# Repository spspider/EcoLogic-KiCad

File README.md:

# EcoLogic KiCad - ESP8266 Home Automation PCB

A professional-grade KiCad project for ESP8266-based home automation systems, designed for PCBWAY manufacturing and Home Assistant integration.

you can control your device throw this site:
[https://ecologic.pp.ua/iot-manager/](https://ecologic.pp.ua/iot-manager/)
Register as a new user and go to "Devices"

## 📋 Project Overview

This repository contains complete PCB designs for IoT home automation controllers using ESP8266 microcontrollers. The boards are optimized for controlling lights, home appliances, and other smart devices through Home Assistant.

### Key Features
- ESP8266-based design for WiFi connectivity
- Multiple relay outputs for appliance control
- PCBWAY-ready manufacturing files
- Home Assistant compatible
- Professional PCB layout with proper isolation
- SMD components for compact design

## 🖼️ Board Images

| Schematic | PCB Layout |
|-----------|------------|
|  |  |
|  |  |

## 📁 Repository Structure

```
EcoLogic-KiCad/
├── IoTmanager/                    # Main project directory
│   ├── BOM-CPL/                   # Bill of Materials & Component Placement
│   │   ├── BOM.csv               # PCBWAY Bill of Materials
│   │   ├── CPL.xlsx              # Component Placement List
│   │   └── *.csv                 # Position files
│   ├── gerber/                    # Manufacturing files
│   │   ├── gerber.zip            # Complete gerber package
│   │   ├── *.gbr                 # Individual gerber layers
│   │   └── *.drl                 # Drill files
│   ├── images/                    # PCB and schematic images
│   ├── LCPCB/                     # PCBWAY templates
│   └── *.kicad_*                 # KiCad project files
└── README.md                      # This file
```

## 🔧 Bill of Materials (BOM)

| Reference | Component | Quantity | Description |
|-----------|-----------|----------|-------------|
| U2 | ESP-12F | 1 | ESP8266 WiFi Module |
| U6 | AMS1117-3.3 | 1 | 3.3V Voltage Regulator |
| U12 | AMS1117-5.0 | 1 | 5.0V Voltage Regulator |
| U3 | DHT11 | 1 | Temperature & Humidity Sensor |
| U7 | DS18B20 | 1 | Temperature Sensor |
| U5 | PJ-320A | 1 | Audio Jack Connector |
| Q1,Q3,Q5,Q7 | MMBT5401 | 4 | PNP Transistors |
| Q2,Q4,Q6,Q8 | MMBT5551-npn | 4 | NPN Transistors |
| K3,K5,K6,K7 | ZC32F-012-HS3 | 4 | 12V Relays |
| D1 | LD271 | 1 | LED Indicator |
| D2,D3,D4,D5 | 1N4148 | 4 | Switching Diodes |
| C1,C2 | 1000µF | 2 | Polarized Capacitors |
| C4 | 10µF | 1 | Polarized Capacitor |
| C3 | 100nF | 1 | Ceramic Capacitor |
| R1,R5,R8,R11,R16 | 100Ω | 5 | Current Limiting Resistors |
| R3,R4,R12,R14-R19 | 1kΩ | 10 | Base Resistors |
| R2,R6,R9,R10,R13 | 10kΩ | 8 | Pull-up Resistors |
| R7 | 4.7kΩ | 1 | Pull-up Resistor |
| 33R1 | 33Ω | 1 | Current Limiting Resistor |
| J1 | Power Relay | 1 | Main Power Connector |
| J2,J3 | 12-Pin Connector | 2 | I/O Connectors |
| J4 | Flash Connector | 1 | Programming Interface |
| J5 | Reset Button | 1 | System Reset |
| SW1 | Push Button | 1 | 6mm Tactile Switch |
| Jumper-d5,d6,d7 | Jumpers | 3 | Configuration Jumpers |

## 🏭 PCBway Manufacturing Guide

### Step 1: Prepare Files
1. Download the complete `gerber.zip` from `IoTmanager/gerber/`
2. Get BOM file: `IoTmanager/BOM-CPL/BOM.csv`
3. Get CPL file: `IoTmanager/BOM-CPL/CPL.xlsx`

### Step 2: Upload to PCBWAY
1. Go to [www.pcbway.com](https://www.pcbway.com/QuickOrderOnline.aspx)

2. Click "Add gerber file" and upload `gerber2.zip`
3. Review PCB specifications, dont change anything:

   - **Layers**: 2
   - **Thickness**: 1.6mm
   - **Color**: Green (recommended)
   - **Surface Finish**: HASL (lead-free)

### Step 3: SMT Assembly (Optional)
1. Enable "SMT Assembly"
2. Upload BOM file (`BOM.csv`)
3. Upload CPL file (`CPL.xlsx`)
4. Review component placement
5. Confirm parts availability

### Step 4: Order
- Minimum quantity: 5 pieces
- Typical lead time: 2-5 days (PCB only)
- SMT assembly adds 3-5 days

## ⚡ Power Requirements

| Parameter | Value | Notes |
|-----------|-------|-------|
| Input Voltage | 5V DC | Via USB or external supply |
| Current Consumption | 80-200mA | Depends on relay states |
| Relay Switching | 10A @ 250V AC | Per relay channel |
| Logic Level | 3.3V | ESP8266 native |

## 🛠️ Assembly Tips

### Soldering Guidelines
- Use lead-free solder (SAC305 recommended)
- Soldering iron: 350°C for SMD components
- Use flux for better joints
- Solder ESP8266 module first

### Testing Procedure
1. **Visual Inspection**: Check for shorts and proper alignment
2. **Power Test**: Apply 5V and measure 3.3V rail
3. **Programming Test**: Upload basic blink sketch
4. **Relay Test**: Verify relay switching with multimeter

## 🚨 Safety Warnings

⚠️ **HIGH VOLTAGE WARNING**
- Relays switch mains voltage (110V/220V AC)
- Always disconnect power before wiring
- Use proper electrical enclosure
- Follow local electrical codes

⚠️ **ESD Precautions**
- Use anti-static wrist strap during assembly
- Store boards in anti-static bags
- Ground yourself before handling

## 📝 Version History

| Version | Date | Changes |
|---------|------|---------|
| v2 | 2025-07 | Improved routing, added protection circuits |
| v1 | 2025-05 | Initial release |

## 🤝 Contributing

1. Fork the repository
2. Create feature branch (`git checkout -b feature/improvement`)
3. Commit changes (`git commit -am 'Add improvement'`)
4. Push to branch (`git push origin feature/improvement`)
5. Create Pull Request

## 📄 License

This project is open-source hardware. Feel free to modify and distribute according to your needs.

## 🆘 Support & Donations

If this project helped you, consider supporting the development:

**Other ways to support:**
- ⭐ Star this repository
- 🐛 Report bugs and issues
- 💡 Suggest improvements
- 📖 Improve documentation
---

**Made with ❤️ for the Home Automation Community**

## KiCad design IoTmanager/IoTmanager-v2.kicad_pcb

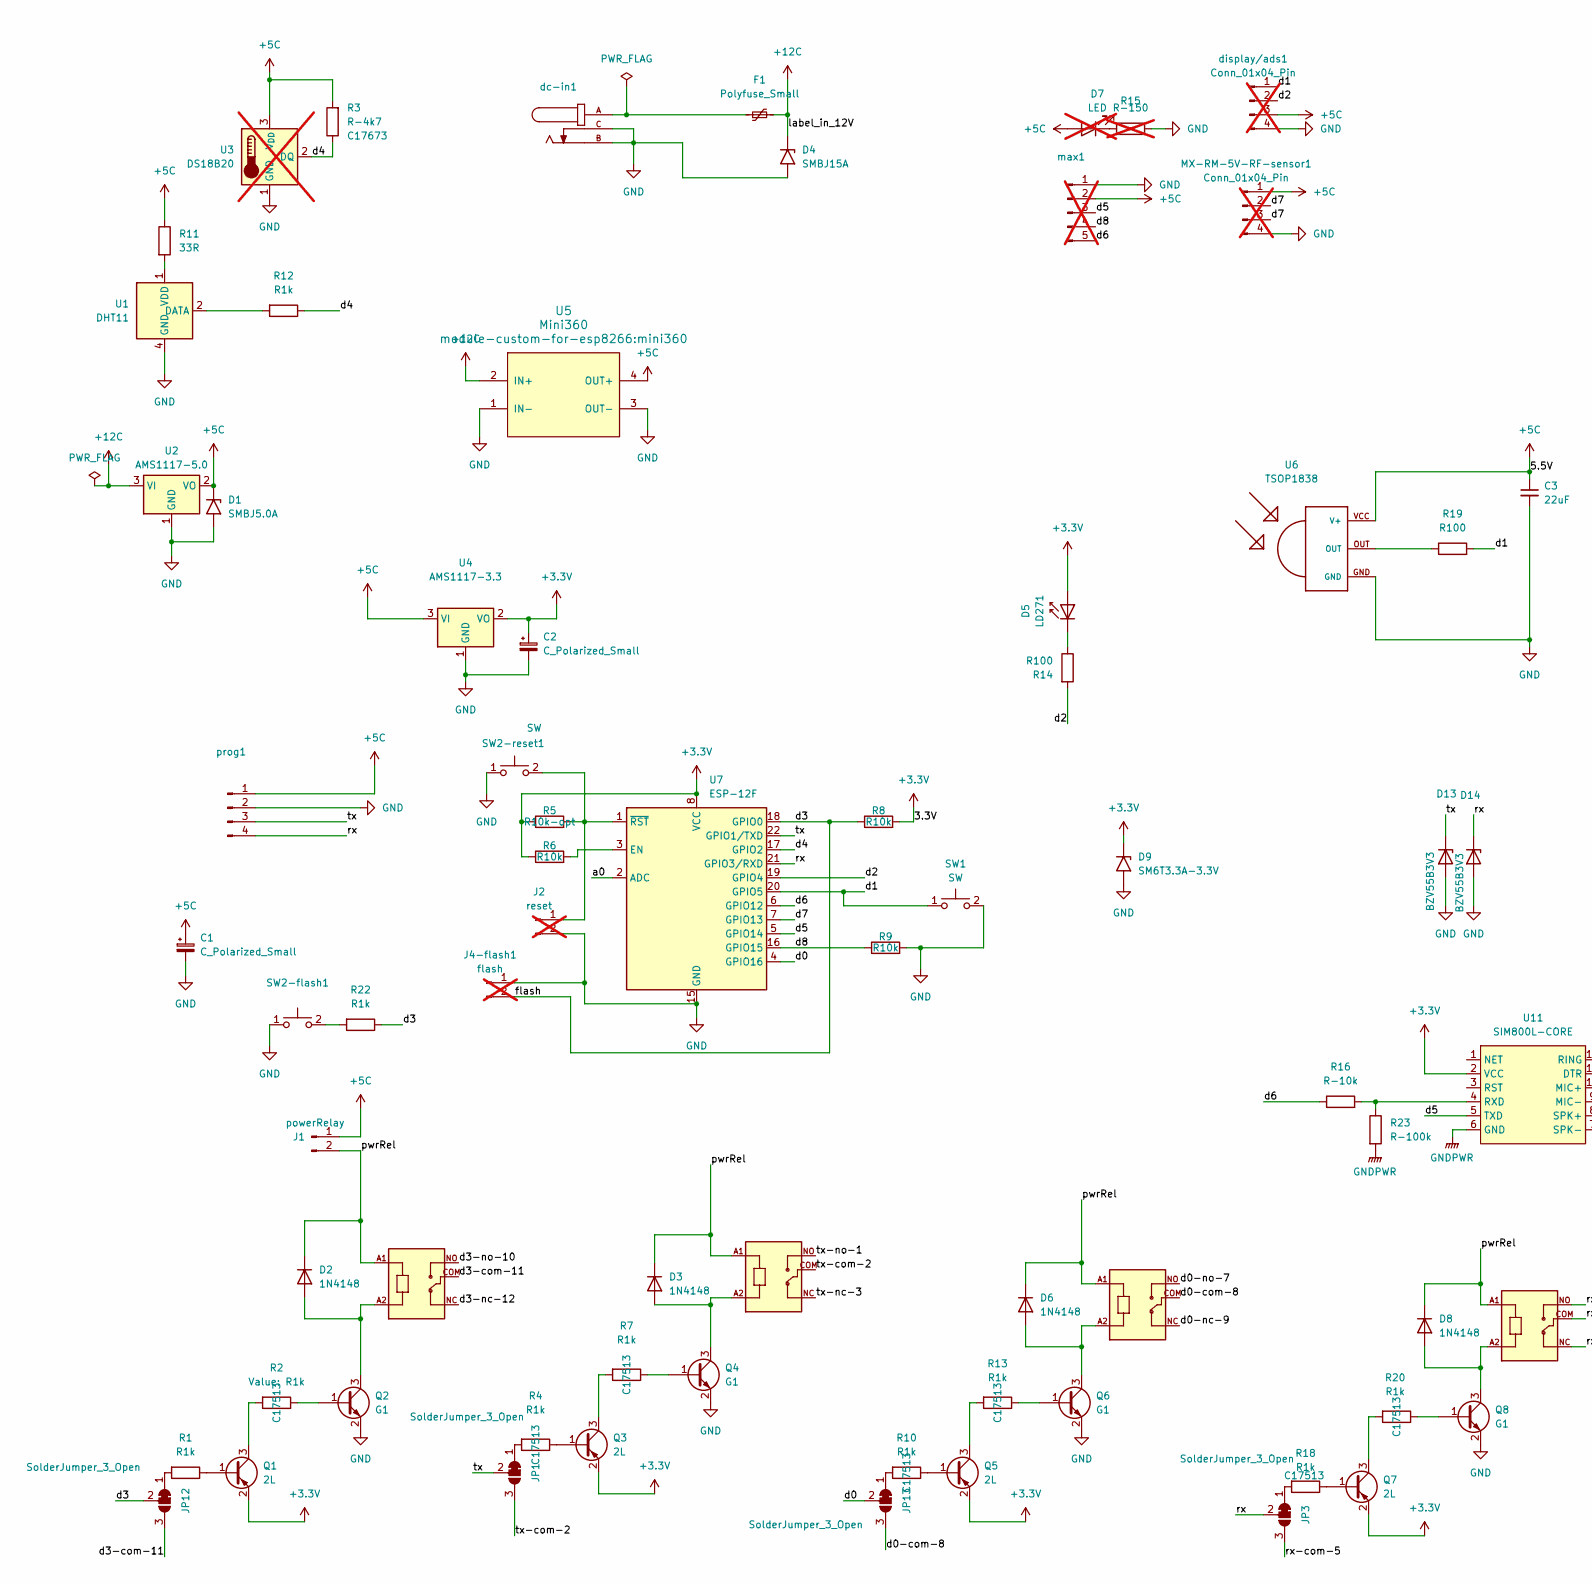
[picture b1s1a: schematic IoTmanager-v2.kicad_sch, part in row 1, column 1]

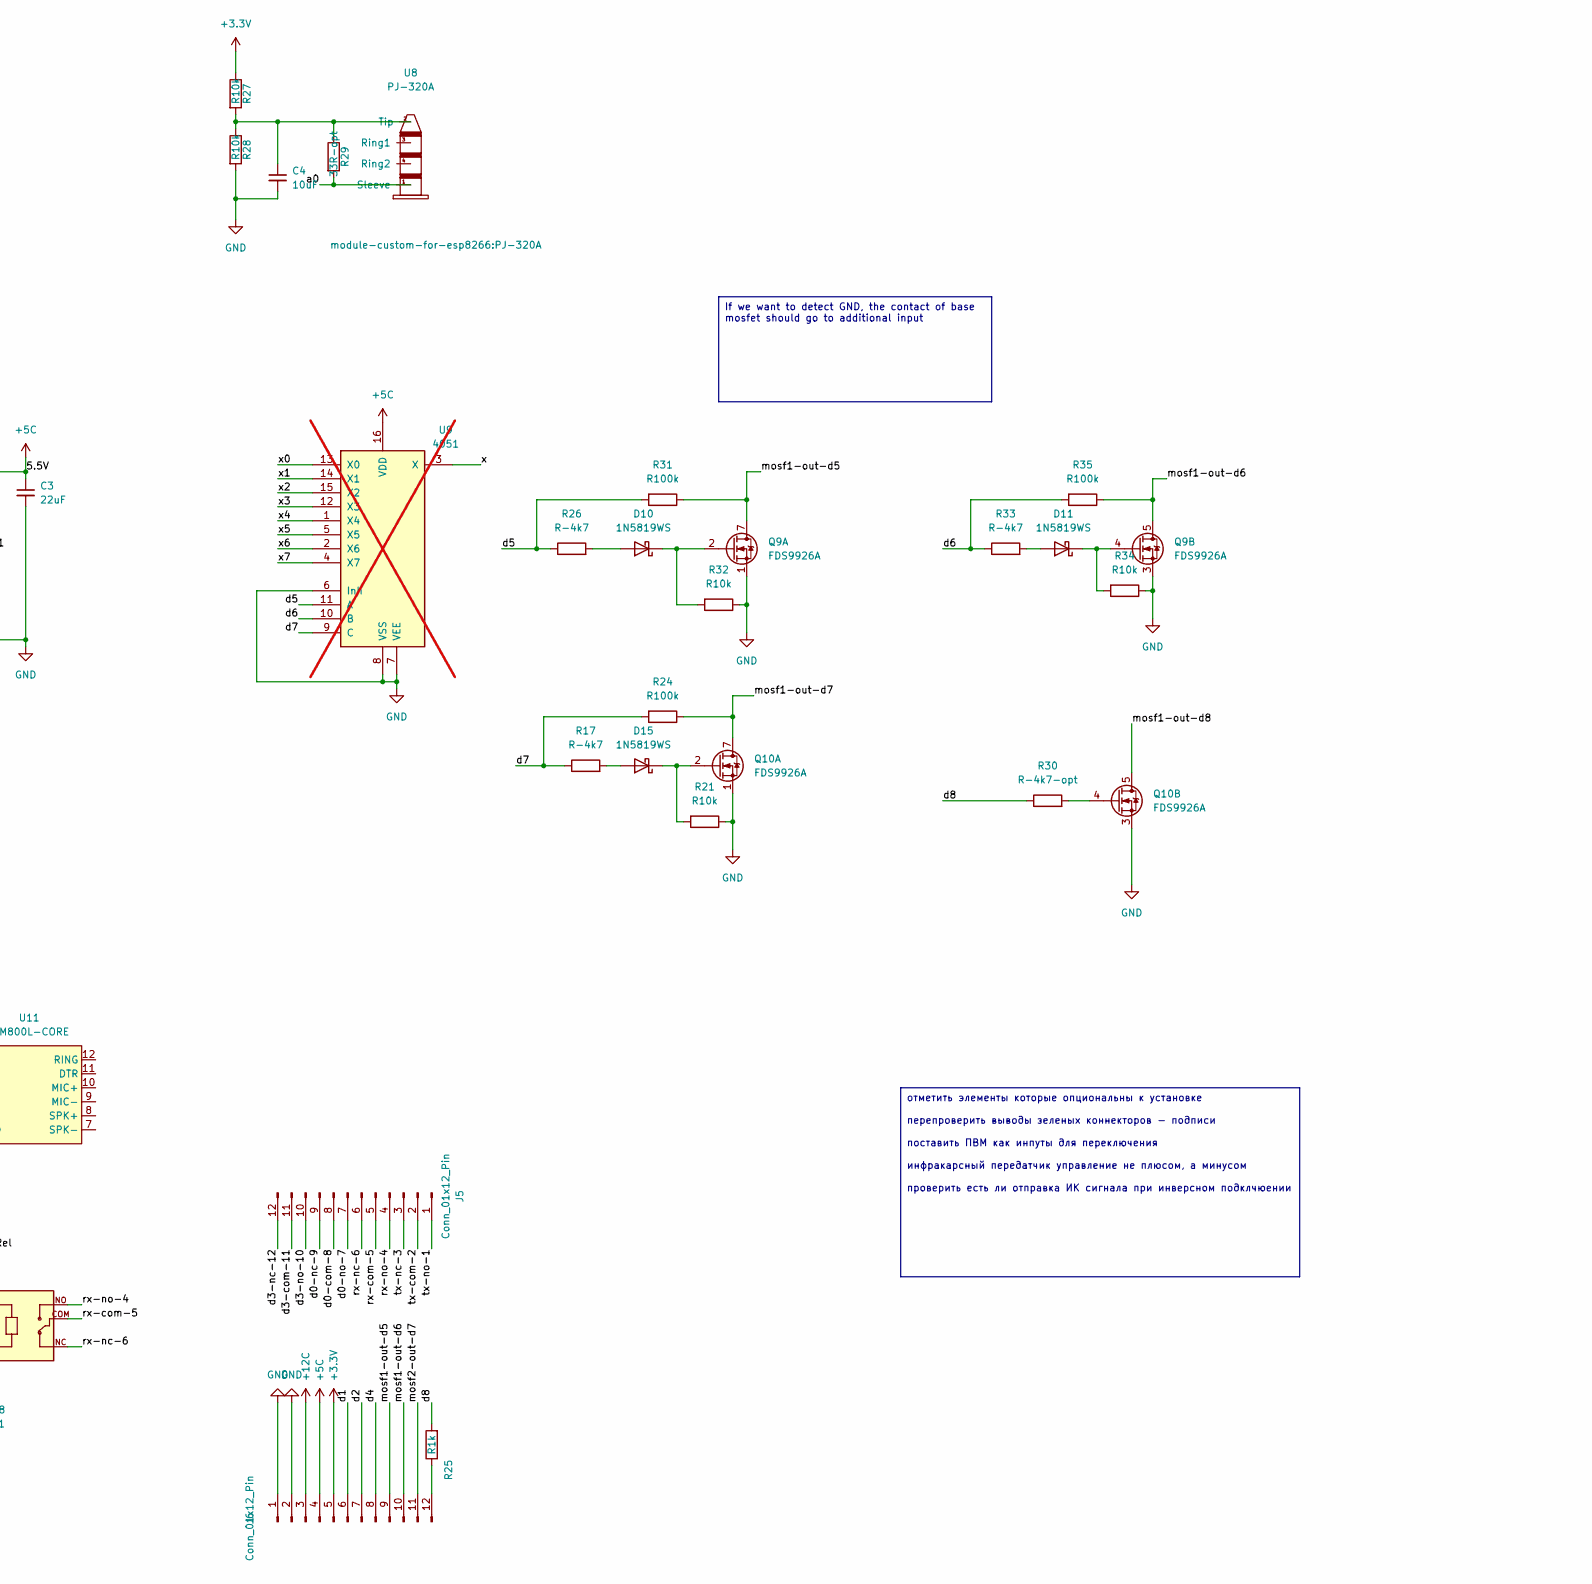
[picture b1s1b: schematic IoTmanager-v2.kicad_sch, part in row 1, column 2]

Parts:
C1, C2: C_Polarized_Small; CP_Radial_D10.0mm_P3.50mm
C3: 22uF; C_0805_2012Metric_Pad1.18x1.45mm_HandSolder; JLCPCB Part C45783
C4: 10uF; C_0805_2012Metric_Pad1.18x1.45mm_HandSolder; JLCPCB Part C15850
D1: SMBJ5.0A; D_SMB
D2, D3, D6, D8: 1N4148; D_MiniMELF
D4: SMBJ15A; D_SMB
D5: LD271; LED_D5.0mm_IRGrey
D7: LED; LED_D5.0mm; not fitted
D9: SM6T3.3A-3.3V; D_SMB
D10, D11, D15: 1N5819WS; D_SOD-123
D13, D14: BZV55B3V3; D_MiniMELF
F1: Polyfuse_Small; Fuse_1812_4532Metric
J1: powerRelay; PinHeader_1x02_P2.54mm_Vertical
J2: reset; PinHeader_1x02_P2.54mm_Vertical; not fitted
J4-flash1: flash; PinHeader_1x02_P2.54mm_Vertical; not fitted
J5, J6: Conn_01x12_Pin; connector-12-green-mini
JP1, JP3, JP12, JP13: SolderJumper_3_Open; SolderJumper-3_P1.3mm_Bridged12_RoundedPad1.0x1.5mm
K1, K2, K3, K4: RELAY_SRD-05VDC; RELAY_SRD-05VDC-SL-C
MX-RM-5V-RF-sensor1: Conn_01x04_Pin; RF_Receiver_433_MHz; not fitted
Q1, Q3, Q5, Q7: 2L; SOT-23; LCSC Part C8326
Q2, Q4, Q6, Q8: G1; SOT-23; LCSC Part C2145
Q9, Q10: FDS9926A; SOIC-8_3.9x4.9mm_P1.27mm
R1, R2, R4, R7, R10, R13, R18, R20, R22: R1k; C_0805_2012Metric_Pad1.18x1.45mm_HandSolder; LCSC Part C25905
R3: R-4k7; C_0805_2012Metric_Pad1.18x1.45mm_HandSolder; JLCPCB Part C17673
R5: R10k-opt; C_0805_2012Metric_Pad1.18x1.45mm_HandSolder; LCSC Part C17414
R6, R8, R9, R27, R28, R32: R10k; C_0805_2012Metric_Pad1.18x1.45mm_HandSolder; LCSC Part C17414
R11: 33R; C_0805_2012Metric_Pad1.18x1.45mm_HandSolder; LCSC Part C17414
R12, R25: R1k; C_0805_2012Metric_Pad1.18x1.45mm_HandSolder; LCSC Part C17414
R14, R19: R100; C_0805_2012Metric_Pad1.18x1.45mm_HandSolder; LCSC Part C17408
R15: R-150; C_0805_2012Metric_Pad1.18x1.45mm_HandSolder; LCSC Part C17408; not fitted
R16: R-10k; R_0805_2012Metric; JLCPCB Part C17414
R17, R26, R33: R-4k7; R_0805_2012Metric; LCSC Part C17408
R21, R34: R10k; R_0805_2012Metric; LCSC Part C17414
R23: R-100k; R_0805_2012Metric; JLCPCB Part C17414
R24, R31, R35: R100k; R_0805_2012Metric; LCSC Part C17414
R29: 33R-opt; C_0805_2012Metric_Pad1.18x1.45mm_HandSolder; LCSC Part C17414
R30: R-4k7-opt; R_0805_2012Metric; LCSC Part C17408
SW1, SW2-flash1, SW2-reset1: SW; SW_PUSH_6mm_H4.3mm
U1: DHT11; Aosong_DHT11_5.5x12.0_P2.54mm
U2: AMS1117-5.0; SOT-223-3_TabPin2; LCSC Part C6187
U3: DS18B20; TO-92_Inline; LCSC Part C20611523; not fitted
U4: AMS1117-3.3; SOT-223-3_TabPin2; LCSC Part C6186
U5: Mini360; mini360
U6: TSOP1838; TSOP18XX
U7: ESP-12F; ESP-12E_no_pins
U8: PJ-320A; LCSC Part C2884926
U9: 4051; SOP-16_3.9x9.9mm_P1.27mm; not fitted
U11: SIM800L-CORE
dc-in1: 5.5PowerIn; PARTREV A
display/ads1: Conn_01x04_Pin; PinHeader_1x04_P2.54mm_Vertical; not fitted
max1: PinHeader_1x05_P2.54mm_Vertical; not fitted
prog1: prog; PinHeader_1x04_P2.54mm_Vertical

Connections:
+3.3V: C2.1, D5.2 (A), D9.1 (A1), J6.5, Q1.2 (E), Q3.2 (E), Q5.2 (E), Q7.2 (E), R5.1, R6.1, R8.2, R27.1, U4.2 (VO), U7.8 (VCC), U11.2 (VCC)
+5C: C1.1, C3.1, D1.1 (A1), D7.2 (A), J1.1, J6.4, MX-RM-5V-RF-sensor1.1, R3.2, R11.1, U2.2 (VO), U3.3 (V_{DD}), U4.3 (VI), U5.4 (OUT+), U6.VCC (V+), U9.16 (VDD), display/ads1.3, max1.2, prog1.1
+12C: D4.1 (A1), F1.2, J6.3, U2.3 (VI), U5.2 (IN+)
/a0: R29.2, U7.2 (ADC), U8.1 (Sleeve)
/d0: JP13.2 (C), U7.4 (GPIO16)
/d0-com-8: J5.8, JP13.3 (B), K3.COM
/d0-nc-9: J5.9, K3.NC
/d0-no-7: J5.7, K3.NO
/d1: J6.6, R19.2, SW1.1 (C), U7.20 (GPIO5), display/ads1.1
/d2: J6.7, R14.2, U7.19 (GPIO4), display/ads1.2
/d3: J4-flash1.2, JP12.2 (C), R8.1, R22.1, U7.18 (GPIO0)
/d3-com-11: J5.11, JP12.3 (B), K1.COM
/d3-nc-12: J5.12, K1.NC
/d3-no-10: J5.10, K1.NO
/d4: J6.8, R3.1, R12.1, U3.2 (DQ), U7.17 (GPIO2)
/d5: R26.1, R31.2, U7.5 (GPIO14), U9.11 (A), U11.5 (TXD), max1.3
/d6: R16.1, R33.1, R35.2, U7.6 (GPIO12), U9.10 (B), max1.5
/d7: MX-RM-5V-RF-sensor1.2, MX-RM-5V-RF-sensor1.3, R17.1, R24.2, U7.7 (GPIO13), U9.9 (C)
/d8: R9.1, R25.2, R30.1, U7.16 (GPIO15), max1.4
/mosf1-out-d5: J6.9, Q9.7 (D1), Q9.8 (D1), R31.1
/mosf1-out-d6: J6.10, Q9.5 (D2), Q9.6 (D2), R35.1
/mosf1-out-d7: Q10.7 (D1), Q10.8 (D1), R24.1
/mosf1-out-d8: Q10.5 (D2), Q10.6 (D2)
/mosf2-out-d7: J6.11
/pwrRel: D2.1 (K), D3.1 (K), D6.1 (K), D8.1 (K), J1.2, K1.A1, K2.A1, K3.A1, K4.A1
/rx: D14.1 (K), JP3.2 (C), U7.21 (GPIO3/RXD), prog1.4
/rx-com-5: J5.5, JP3.3 (B), K4.COM
/rx-nc-6: J5.6, K4.NC
/rx-no-4: J5.4, K4.NO
/tx: D13.1 (K), JP1.2 (C), U7.22 (GPIO1/TXD), prog1.3
/tx-com-2: J5.2, JP1.3 (B), K2.COM
/tx-nc-3: J5.3, K2.NC
/tx-no-1: J5.1, K2.NO
GND: C1.2, C2.2, C3.2, C4.2, D1.2 (A2), D4.2 (A2), D9.2 (A2), D13.2 (A), D14.2 (A), J2.2, J4-flash1.1, J6.1, J6.2, MX-RM-5V-RF-sensor1.4, Q2.2 (E), Q4.2 (E), Q6.2 (E), Q8.2 (E), Q9.1 (S1), Q9.3 (S2), Q10.1 (S1), Q10.3 (S2), R9.2, R15.2, R21.1, R28.2, R32.1, R34.1, SW1.2 (D), SW2-flash1.1 (C), SW2-reset1.1 (C), U1.4 (GND), U2.1 (GND), U3.1 (GND), U4.1 (GND), U5.1 (IN-), U5.3 (OUT-), U6.GND, U7.15 (GND), U9.6 (Inh), U9.7 (VEE), U9.8 (VSS), dc-in1.B, dc-in1.C, display/ads1.4, max1.1, prog1.2
GNDPWR: R23.2, U11.6 (GND)
unnamed: D2.2 (A), K1.A2, Q2.3 (C)
unnamed: D3.2 (A), K2.A2, Q4.3 (C)
unnamed: D5.1 (K), R14.1
unnamed: D6.2 (A), K3.A2, Q6.3 (C)
unnamed: D7.1 (K), R15.1
unnamed: D8.2 (A), K4.A2, Q8.3 (C)
unnamed: D10.2 (A), R26.2
unnamed: D10.1 (K), Q9.2 (G1), R32.2
unnamed: D11.2 (A), R33.2
unnamed: D11.1 (K), Q9.4 (G2), R34.2
unnamed: D15.2 (A), R17.2
unnamed: D15.1 (K), Q10.2 (G1), R21.2
unnamed: F1.1, dc-in1.A
unnamed: J6.12, R25.1
unnamed: JP1.1 (A), R4.2
unnamed: JP3.1 (A), R18.2
unnamed: JP12.1 (A), R1.2
unnamed: JP13.1 (A), R10.2
unnamed: Q1.1 (B), R1.1
unnamed: Q1.3 (C), R2.2
unnamed: Q2.1 (B), R2.1
unnamed: Q3.1 (B), R4.1
unnamed: Q3.3 (C), R7.2
unnamed: Q4.1 (B), R7.1
unnamed: Q5.1 (B), R10.1
unnamed: Q5.3 (C), R13.2
unnamed: Q6.1 (B), R13.1
unnamed: Q7.1 (B), R18.1
unnamed: Q7.3 (C), R20.2
unnamed: Q8.1 (B), R20.1
unnamed: Q10.4 (G2), R30.2
unnamed: R19.1, U6.OUT
unnamed: R22.2, SW2-flash1.2 (D)
unnamed: J2.1, R5.2, SW2-reset1.2 (D), U7.1 (~RST)
unnamed: R12.2, U1.2 (DATA)
unnamed: R11.2, U1.1 (VDD)
unnamed: R6.2, U7.3 (EN)
unnamed: C4.1, R27.2, R28.1, R29.1, U8.2 (Tip)
unnamed: R16.2, R23.1, U11.4 (RXD)

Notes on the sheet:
отметить элементы которые опциональны к установке перепроверить выводы зеленых коннекторов - подписи поставить ПВМ как инпуты для переключения инфракарсный передатчик управление не плюсом, а минусом проверить есть ли отправка ИК сигнала при инверсном подклчюении
If we want to detect GND, the contact of base mosfet should go to additional input

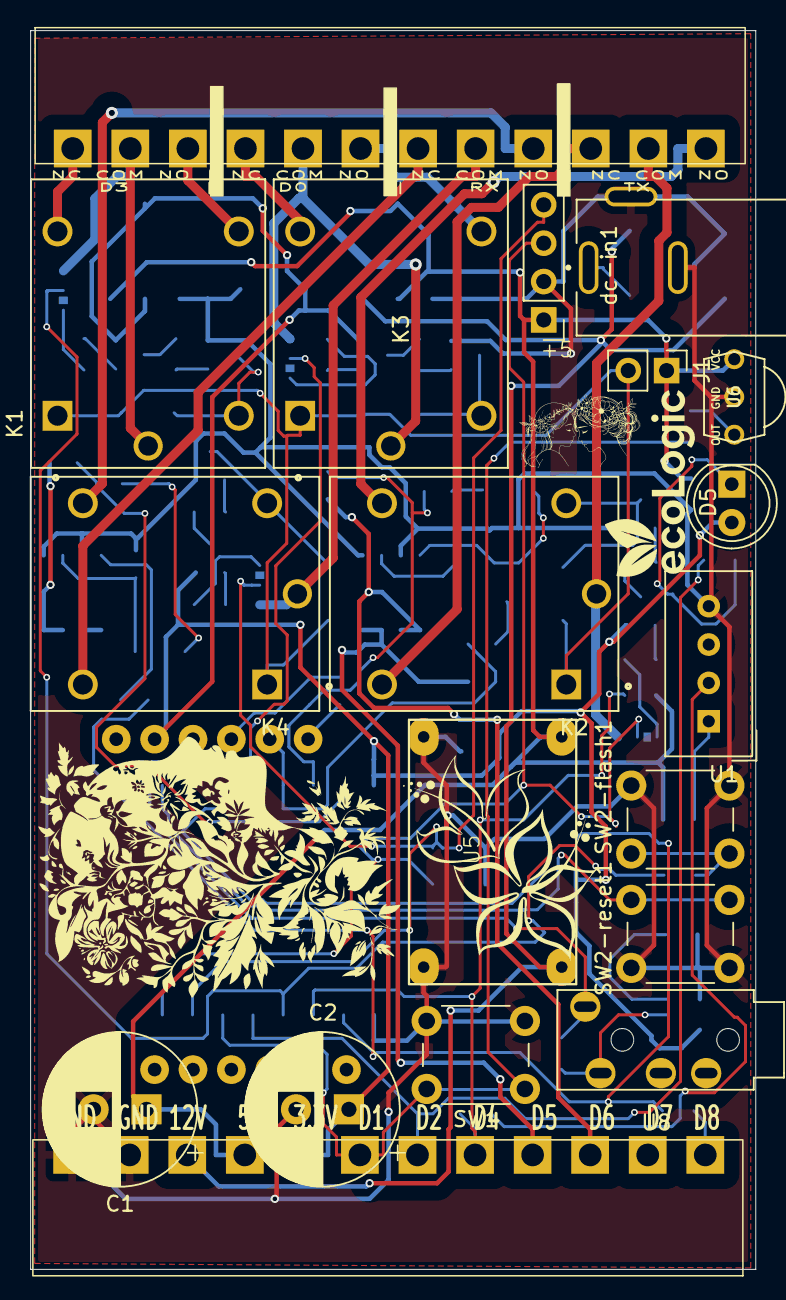
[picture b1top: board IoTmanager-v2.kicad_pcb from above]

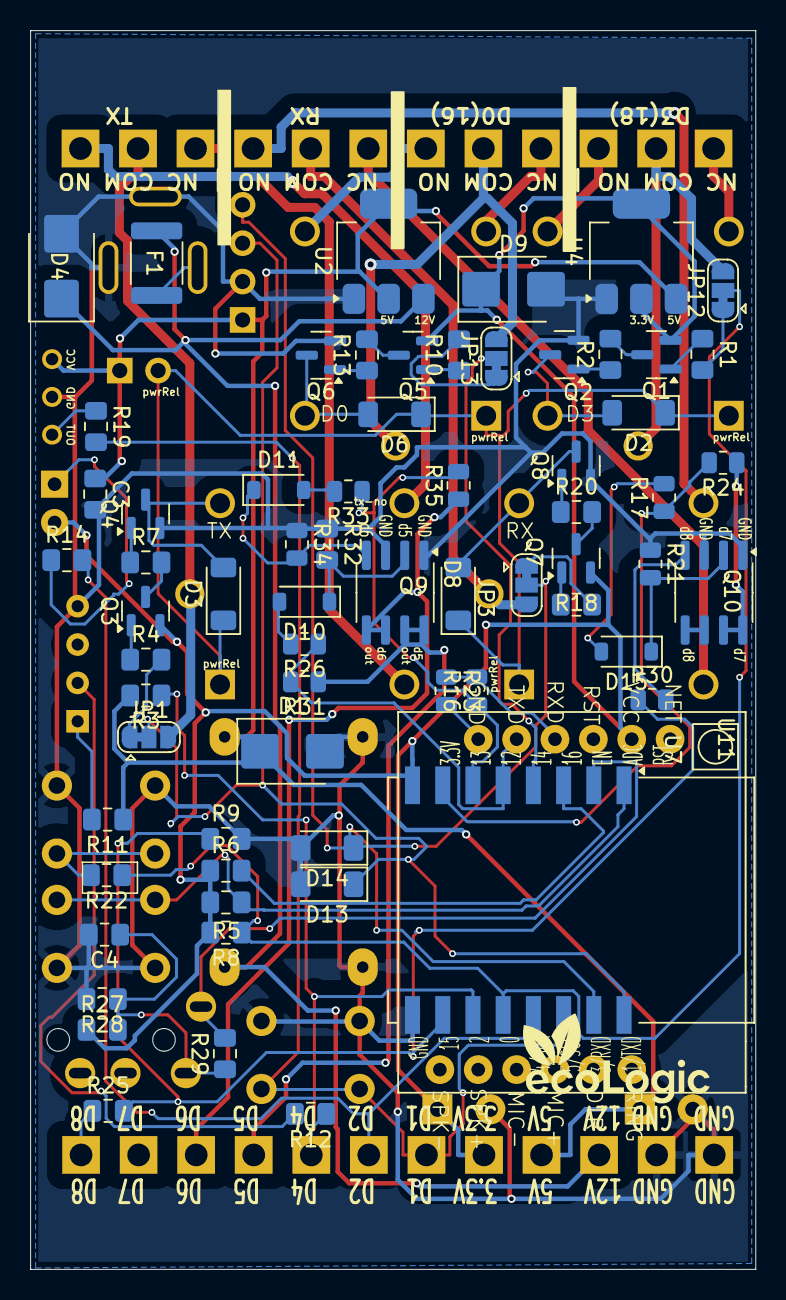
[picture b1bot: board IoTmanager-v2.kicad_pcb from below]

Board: 2 copper layers, 48.0 x 82.0 mm, 91 parts (68 on the bottom side), 72 nets.

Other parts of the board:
G2, G3: LOGO
flowers: LOGO
woman: LOGO
womans: LOGO

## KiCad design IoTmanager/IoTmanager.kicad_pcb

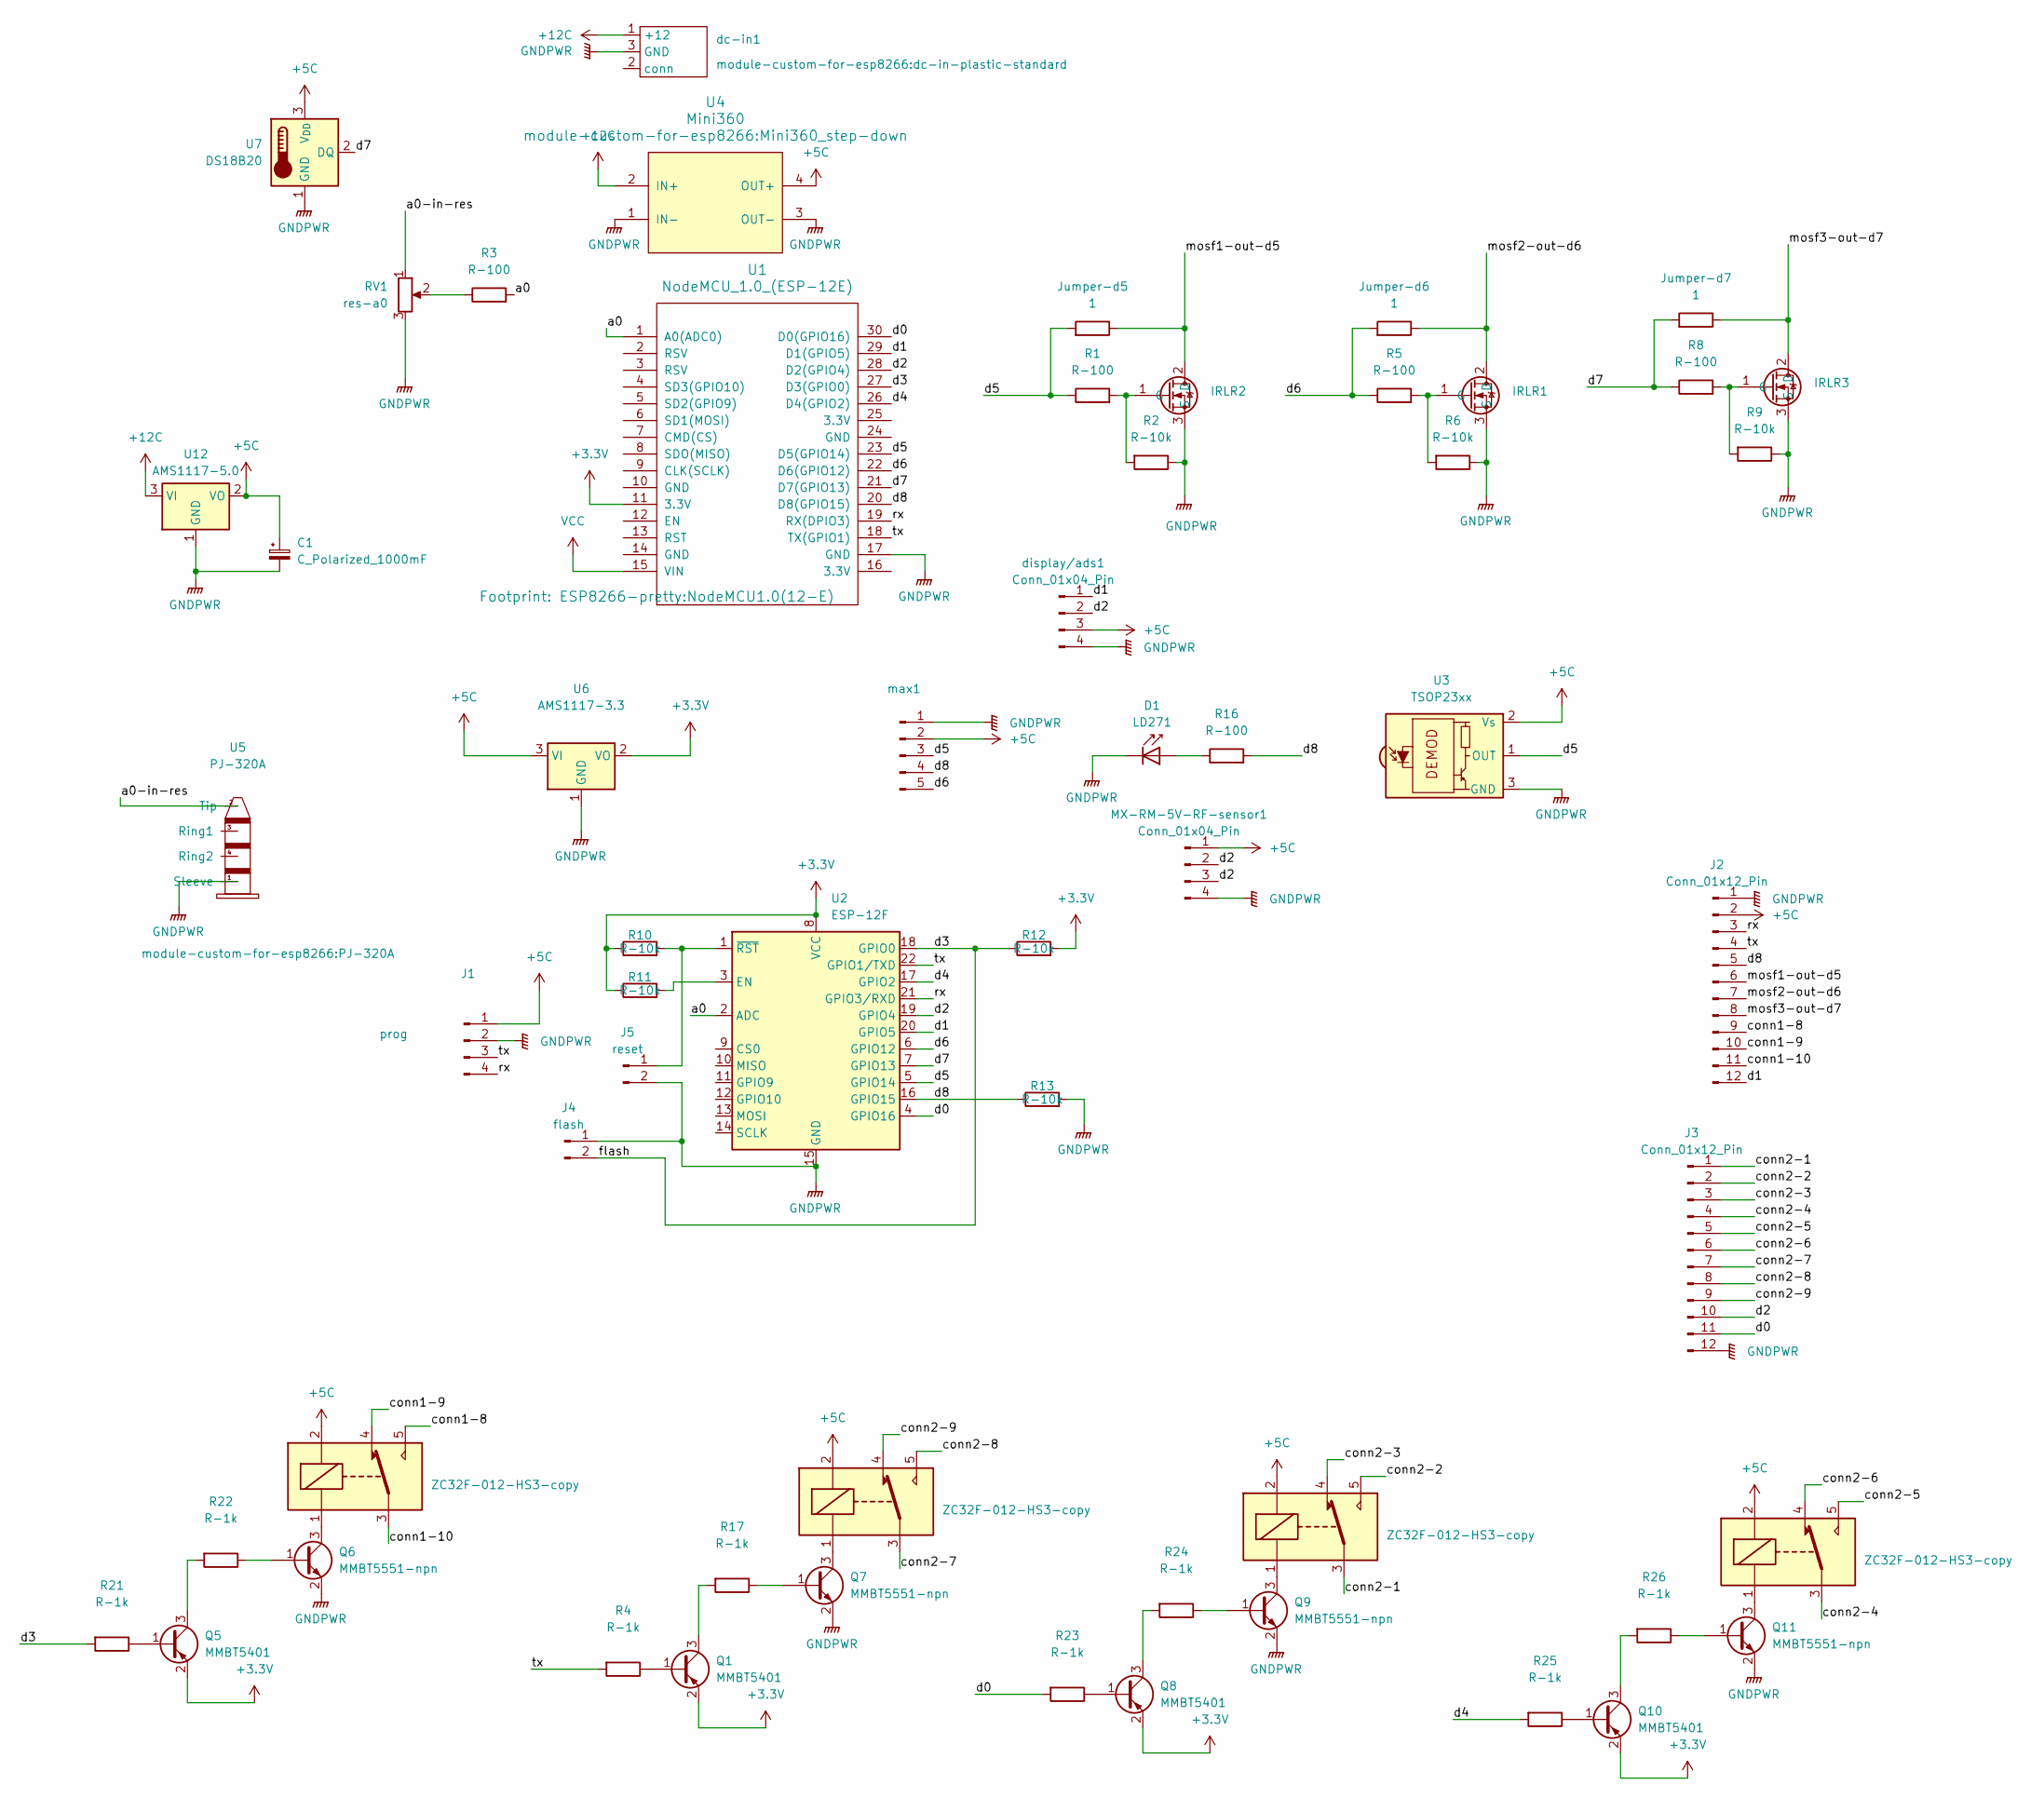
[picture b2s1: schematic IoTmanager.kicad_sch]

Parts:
C1: C_Polarized_1000mF; CP_Radial_D10.0mm_P3.50mm
D1: LD271; LED_D5.0mm_IRGrey
IRLR1, IRLR2, IRLR3: TO-252-2
J1: prog; PinHeader_1x04_P2.54mm_Vertical
J2, J3: Conn_01x12_Pin; connector-12-green-mini
J4: flash; PinHeader_1x02_P2.54mm_Vertical
J5: reset; PinHeader_1x02_P2.54mm_Vertical
Jumper-d5, Jumper-d6, Jumper-d7: 1; R_0805_2012Metric
K3, K5, K6, K7: ZC32F-012-HS3-copy; ZC32F-012-HS3
MX-RM-5V-RF-sensor1: Conn_01x04_Pin; RF_Receiver_433_MHz
Q1, Q5, Q8, Q10: MMBT5401; SOT-23; LCSC Part C8326
Q6, Q7, Q9, Q11: MMBT5551-npn; SOT-23; LCSC Part C2145
R1, R3, R5, R8, R16: R-100; R_0805_2012Metric; LCSC Part C17408
R2, R6, R9, R10, R11, R12, R13: R-10k; R_0805_2012Metric; LCSC Part C17414
R4, R17, R21, R22, R23, R24, R25, R26: R-1k; R_0805_2012Metric; LCSC Part C25905
RV1: res-a0; Potentiometer_Bourns_3266Y_Vertical
U1: NodeMCU_1.0_(ESP-12E); NodeMCU1.0(12-E)
U2: ESP-12F; ESP-12E
U3: TSOP23xx; Vishay_MOLD-3Pin
U4: Mini360; Mini360_step-down
U5: PJ-320A; LCSC Part C2884926
U6: AMS1117-3.3; SOT-223-3_TabPin2; LCSC Part C6186
U7: DS18B20; TO-92_Inline; LCSC Part C20611523
U12: AMS1117-5.0; SOT-223-3_TabPin2; LCSC Part C6187
dc-in1: dc-in-plastic-standard
display/ads1: Conn_01x04_Pin; PinHeader_1x04_P2.54mm_Vertical
max1: PinHeader_1x05_P2.54mm_Vertical

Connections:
+3.3V: Q1.2 (E), Q5.2 (E), Q8.2 (E), Q10.2 (E), R10.1, R11.1, R12.2, U1.11 (3.3V), U2.8 (VCC), U6.2 (VO)
+5C: C1.1, J1.1, J2.2, K3.2, K5.2, K6.2, K7.2, MX-RM-5V-RF-sensor1.1, U3.2 (Vs), U4.4 (OUT+), U6.3 (VI), U7.3 (V_{DD}), U12.2 (VO), display/ads1.3, max1.2
+12C: U4.2 (IN+), U12.3 (VI), dc-in1.1 (+12)
/a0: R3.2, U1.1 (A0(ADC0)), U2.2 (ADC)
/a0-in-res: RV1.1, U5.2 (Tip)
/conn1-8: J2.9, K3.5
/conn1-9: J2.10, K3.4
/conn1-10: J2.11, K3.3
/conn2-1: J3.1, K6.3
/conn2-2: J3.2, K6.5
/conn2-3: J3.3, K6.4
/conn2-4: J3.4, K7.3
/conn2-5: J3.5, K7.5
/conn2-6: J3.6, K7.4
/conn2-7: J3.7, K5.3
/conn2-8: J3.8, K5.5
/conn2-9: J3.9, K5.4
/d0: J3.11, R23.2, U1.30 (D0(GPIO16)), U2.4 (GPIO16)
/d1: J2.12, U1.29 (D1(GPIO5)), U2.20 (GPIO5), display/ads1.1
/d2: J3.10, MX-RM-5V-RF-sensor1.2, MX-RM-5V-RF-sensor1.3, U1.28 (D2(GPIO4)), U2.19 (GPIO4), display/ads1.2
/d3: J4.2, R12.1, R21.2, U1.27 (D3(GPIO0)), U2.18 (GPIO0)
/d4: R25.2, U1.26 (D4(GPIO2)), U2.17 (GPIO2)
/d5: Jumper-d5.1, R1.1, U1.23 (D5(GPIO14)), U2.5 (GPIO14), U3.1 (OUT), max1.3
/d6: Jumper-d6.1, R5.1, U1.22 (D6(GPIO12)), U2.6 (GPIO12), max1.5
/d7: Jumper-d7.1, R8.1, U1.21 (D7(GPIO13)), U2.7 (GPIO13), U7.2 (DQ)
/d8: J2.5, R13.1, R16.2, U1.20 (D8(GPIO15)), U2.16 (GPIO15), max1.4
/mosf1-out-d5: IRLR2.2 (D), J2.6, Jumper-d5.2
/mosf2-out-d6: IRLR1.2 (D), J2.7, Jumper-d6.2
/mosf3-out-d7: IRLR3.2 (D), J2.8, Jumper-d7.2
/rx: J1.4, J2.3, U1.19 (RX(DPIO3)), U2.21 (GPIO3/RXD)
/tx: J1.3, J2.4, R4.2, U1.18 (TX(GPIO1)), U2.22 (GPIO1/TXD)
GNDPWR: C1.2, D1.1 (K), IRLR1.3 (S), IRLR2.3 (S), IRLR3.3 (S), J1.2, J2.1, J3.12, J4.1, J5.2, MX-RM-5V-RF-sensor1.4, Q6.2 (E), Q7.2 (E), Q9.2 (E), Q11.2 (E), R2.1, R6.1, R9.1, R13.2, RV1.3, U1.17 (GND), U2.15 (GND), U3.3 (GND), U4.1 (IN-), U4.3 (OUT-), U5.1 (Sleeve), U6.1 (GND), U7.1 (GND), U12.1 (GND), dc-in1.3 (GND), display/ads1.4, max1.1
unnamed: D1.2 (A), R16.1
unnamed: IRLR1.1 (G), R5.2, R6.2
unnamed: IRLR2.1 (G), R1.2, R2.2
unnamed: IRLR3.1 (G), R8.2, R9.2
unnamed: J5.1, R10.2, U2.1 (~RST)
unnamed: Q1.1 (B), R4.1
unnamed: Q1.3 (C), R17.2
unnamed: Q5.1 (B), R21.1
unnamed: Q5.3 (C), R22.2
unnamed: Q6.1 (B), R22.1
unnamed: K3.1, Q6.3 (C)
unnamed: Q7.1 (B), R17.1
unnamed: K5.1, Q7.3 (C)
unnamed: Q8.1 (B), R23.1
unnamed: Q8.3 (C), R24.2
unnamed: Q9.1 (B), R24.1
unnamed: K6.1, Q9.3 (C)
unnamed: Q10.1 (B), R25.1
unnamed: Q10.3 (C), R26.2
unnamed: Q11.1 (B), R26.1
unnamed: K7.1, Q11.3 (C)
unnamed: R3.1, RV1.2
unnamed: R11.2, U2.3 (EN)

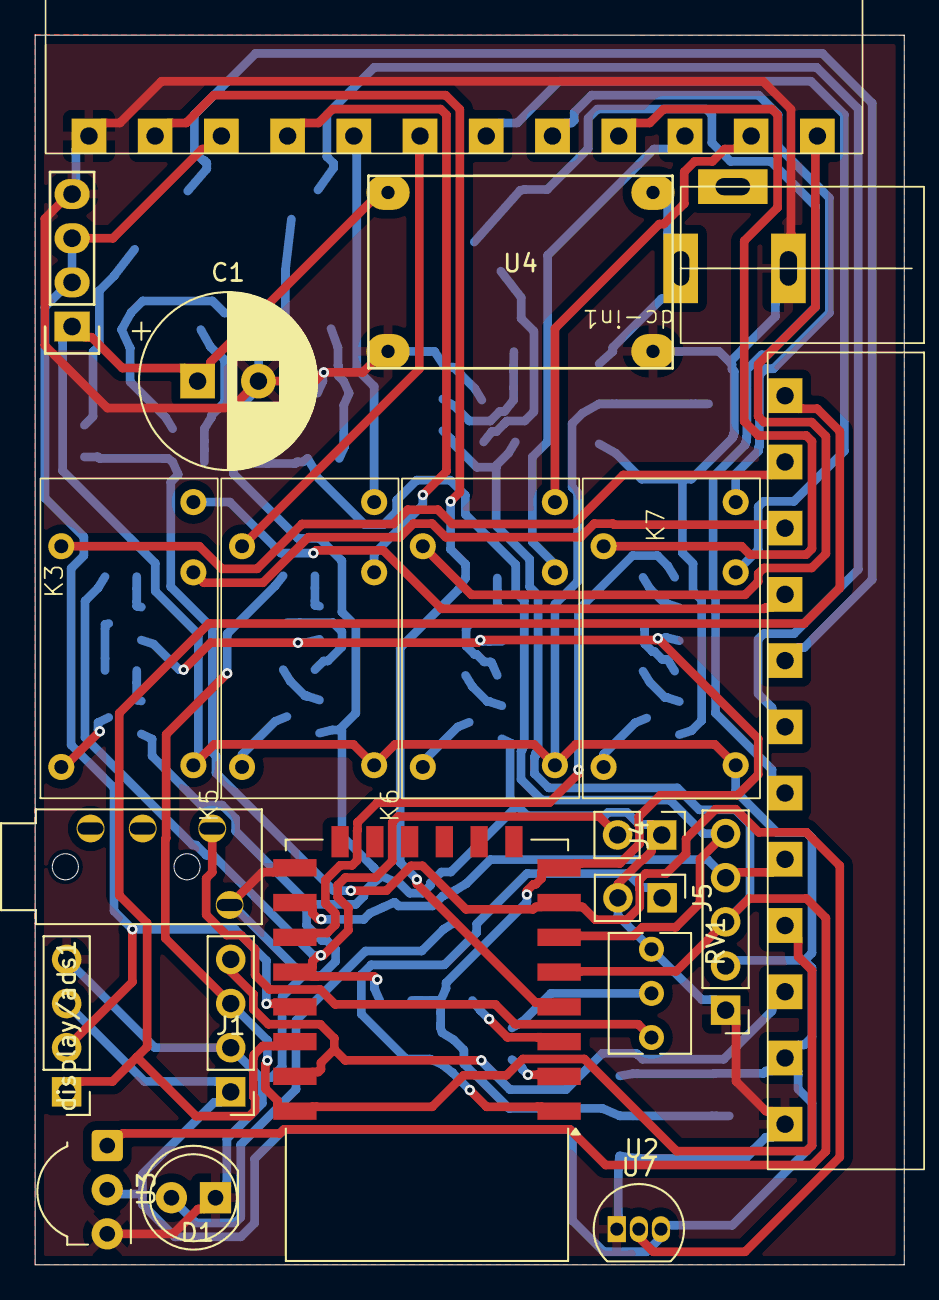
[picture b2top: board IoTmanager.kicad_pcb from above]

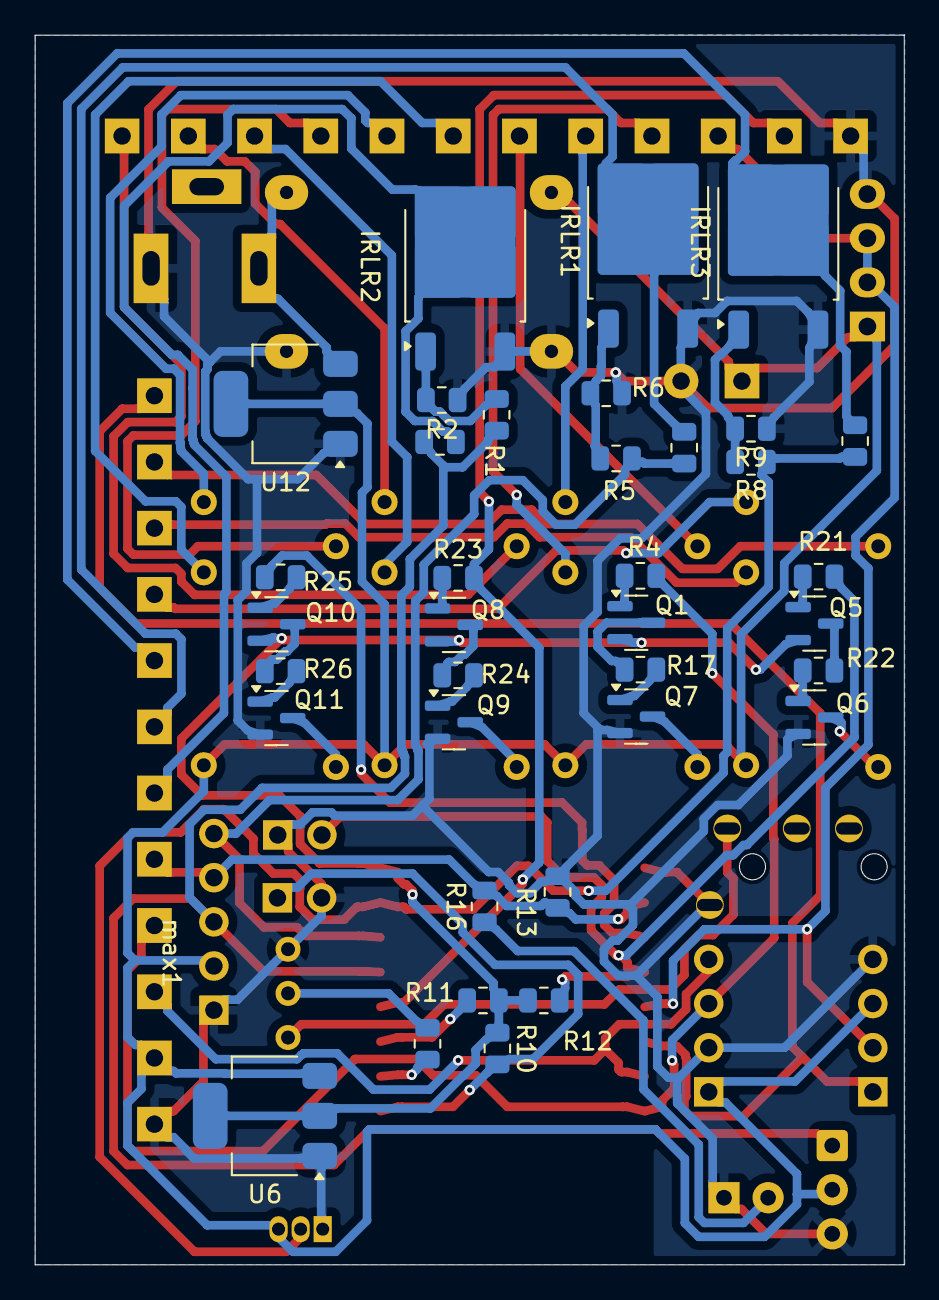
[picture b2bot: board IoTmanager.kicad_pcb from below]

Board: 2 copper layers, 50.0 x 70.7 mm, 57 parts (36 on the bottom side), 55 nets.

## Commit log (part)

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2024-10-19 initial
2024-11-03 remove
2024-11-03 removed
2024-11-09 push
2025-05-24 Update IoTmanager schematic and libraries
    - Changed paper size from A3 to A2 in IoTmanager schematic.
    - Added MMDT4413-7-F symbol and footprint to the schematic and libraries.
    - Updated various component properties including reference, value, and footprint.
    - Adjusted component placements and added new power symbols for +3.3V and GNDPWR.
    - Modified existing project files in Proteous tests, including autosaved versions.
    - Updated fp-info-cache with new component details.
2025-05-30 auto update from EPAM computer
2025-06-16 Update fp-info-cache with new audio module and relay specifications
    - Updated the ID for the Audio_Module entry.
    - Added new relay module (RELAY_SRD-05VDC-SL-C) with specifications.
    - Ensured proper formatting and consistency in the module entries.
2025-06-28 Add additional fields to component metadata in IoTmanager configuration
2025-07-02 Remove obsolete libraries and files for various components including SX1308, EasyDriver, TBD62783, TLE5205, TLP627, TP4056, XL4015, and PJ-320A. This cleanup includes the deletion of associated docum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
2025-07-28 Add new schematic images for IoT manager
2025-07-28 Add new images for IoT manager: plate.png and plate2.png
2025-08-22 Добавить README.md с описанием проекта и инструкциями по сборке
2025-10-04 net and print
2025-10-05 fixed d4
2025-10-16 scheme-instructions
2025-10-19 route design
2025-10-22 moved schema
2025-11-09 bom updates and xls
2025-11-15 wire connectio scheduler
2025-11-22 new route
2025-11-22 BOM XML updated
2025-11-22 rx tx without resistor
2025-11-23 IR fix contact
2025-11-23 new scheme
2025-11-26 pcbway
2025-12-01 new gerber and changes in positions
2025-12-03 3d parametres
2025-12-12 updated BOM
2025-12-12 drawio
2026-01-09 udpate
2026-03-01 update in wires
2026-05-06 added edscription to new version of plate
2026-05-07 added sim800
2026-05-08 text field updates
2026-05-17 fixed route for d1 input
2026-05-17 investigate input output
2026-05-17 trasnsitors and inputs
2026-06-13 Connected
2026-06-26 fixed lables
